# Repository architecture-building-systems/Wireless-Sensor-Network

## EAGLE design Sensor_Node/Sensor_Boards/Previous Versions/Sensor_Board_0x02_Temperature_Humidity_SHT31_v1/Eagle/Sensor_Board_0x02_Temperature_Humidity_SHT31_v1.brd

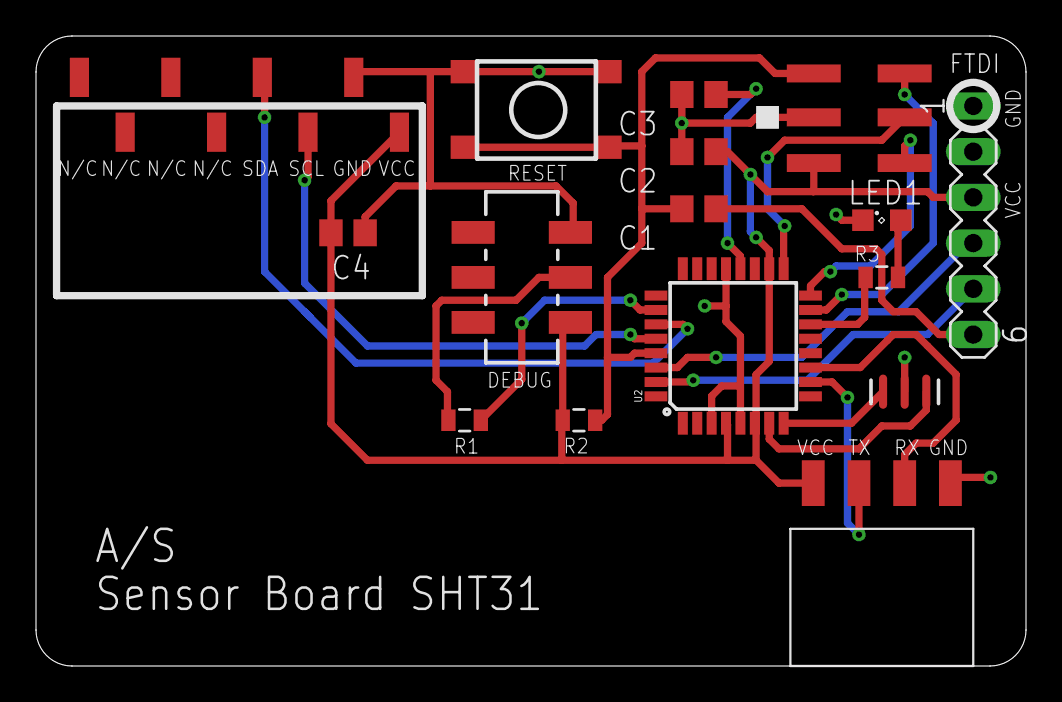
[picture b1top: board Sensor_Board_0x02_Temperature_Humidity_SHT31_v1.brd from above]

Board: 2 copper layers, 55.0 x 35.0 mm, 16 parts (0 on the bottom side), 20 nets.

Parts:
C1, C2, C3, C4: 100n; C0805
J1: M04_SMD_90
J4: ARDUINO_ISP; M-2X3
LED1: Red; SML0805
R1, R2: 10k; 0805
R3: 330; 0805
S1: Reset; M-PUSHBUTTON-SMD
S3: JS202011SCQN
SV1: MA06-1
U2: ATMEGA328P_TQFP; TQFP32-08
U$9: M08_SMD_STRAIGHT
Y1: 8MHZ; RESONATOR-SMD

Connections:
DBG_ENABLE: R1.2, U2.26
FTDI_RESET: C1.1, SV1.6
FTDI_RXI: SV1.4, U2.30
FTDI_TXO: SV1.5, U2.31
GND: C2.2, C3.2, C4.2, J1.4, J4.P$5, LED1.C, S1.1, S1.2, S3.3, SV1.1, SV1.2, U2.3, U2.5, U2.21, U$9.P7, Y1.2
L1: R3.2, U2.14
MCU_RXI: J1.3, U2.11
MCU_TXO: J1.2, U2.10
MISO: J4.P$1, U2.16
MOSI: J4.P$3, U2.15
unnamed: U2.8, Y1.3
unnamed: U2.7, Y1.1
unnamed: R1.1, S3.2
unnamed: C3.1, U2.20
unnamed: LED1.A, R3.1
RESET: C1.2, J4.P$4, R2.1, S1.3, S1.4, U2.29
SCK: J4.P$2, U2.17
SCL: U2.28, U$9.P6
SDA: U2.27, U$9.P5
VCC: C2.1, C4.1, J1.1, J4.P$6, R2.2, S3.1, SV1.3, U2.4, U2.6, U2.18, U$9.P8

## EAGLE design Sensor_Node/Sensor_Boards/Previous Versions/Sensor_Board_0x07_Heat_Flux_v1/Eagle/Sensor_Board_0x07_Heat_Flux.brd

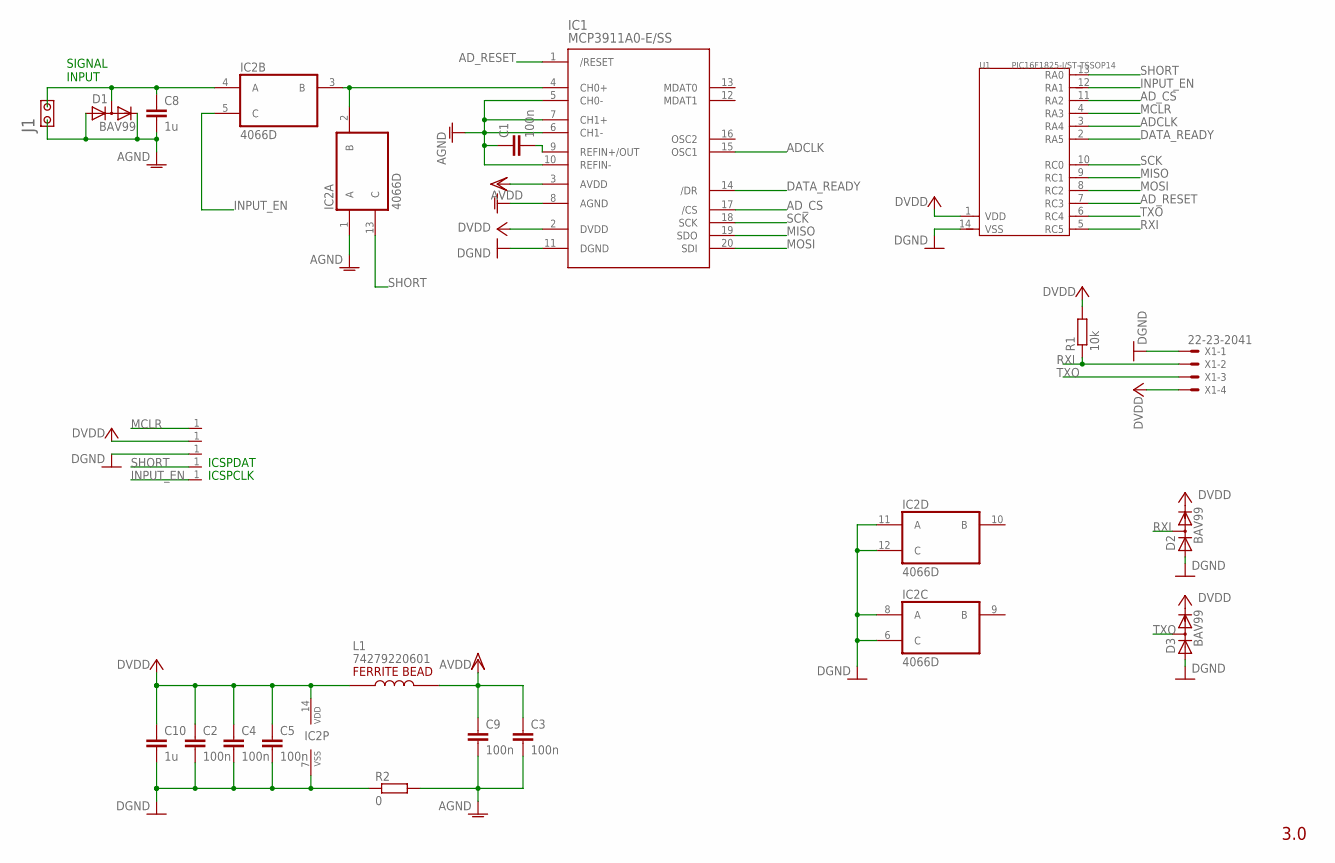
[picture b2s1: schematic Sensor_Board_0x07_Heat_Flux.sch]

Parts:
C1, C2, C3, C4, C5, C9: 100n; C0805
C8, C10: 1u; C0805
D1, D2, D3: BAV99; SOT23
IC1: MCP3911A0-E/SS; SSOP20
IC2: 4066D; SO14
J1: CON2X1
L1: 74279220601; 0805
PIN1, PIN2, PIN3, PIN4, PIN5: CON1X1
R1: 10k; M0805
R2: 0; M0805
U1: PIC16F1825-I/ST-TSSOP14; TSSOP14-0.65-5X4.4MM
X1: 22-23-2041

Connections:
ADCLK: IC1.15 (OSC1), U1.3 (RA4)
AD_CS: IC1.17 (/CS), U1.11 (RA2)
AD_RESET: IC1.1 (/RESET), U1.7 (RC3)
AGND: C1.1, C3.2, C8.2, C9.2, D1.1 (A), D1.2 (C), IC1.5 (CH0-), IC1.6 (CH1-), IC1.7 (CH1+), IC1.8 (AGND), IC1.10 (REFIN-), IC2.1 (A), J1.1, R2.2
AVDD: C3.1, C9.1, IC1.3 (AVDD), L1.2
DATA_READY: IC1.14 (/DR), U1.2 (RA5)
DGND: C2.2, C4.2, C5.2, C10.2, D2.1 (A), D3.1 (A), IC1.11 (DGND), IC2.6 (C), IC2.7 (VSS), IC2.8 (A), IC2.11 (A), IC2.12 (C), PIN3.1, R2.1, U1.14 (VSS), X1.1
DVDD: C2.1, C4.1, C5.1, C10.1, D2.2 (C), D3.2 (C), IC1.2 (DVDD), IC2.14 (VDD), L1.1, PIN2.1, R1.2, U1.1 (VDD), X1.4
INPUT_EN: IC2.5 (C), PIN5.1, U1.12 (RA1)
MCLR: PIN1.1, U1.4 (RA3)
MISO: IC1.19 (SDO), U1.9 (RC1)
MOSI: IC1.20 (SDI), U1.8 (RC2)
unnamed: C1.2, IC1.9 (REFIN+/OUT)
unnamed: IC1.4 (CH0+), IC2.2 (B), IC2.3 (B)
unnamed: C8.1, D1.3 (AC), IC2.4 (A), J1.2
RXI: D2.3 (AC), R1.1, U1.5 (RC5), X1.2
SCK: IC1.18 (SCK), U1.10 (RC0)
SHORT: IC2.13 (C), PIN4.1, U1.13 (RA0)
TXO: D3.3 (AC), U1.6 (RC4), X1.3

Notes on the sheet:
SIGNAL INPUT
ICSPCLK
ICSPDAT
3.0

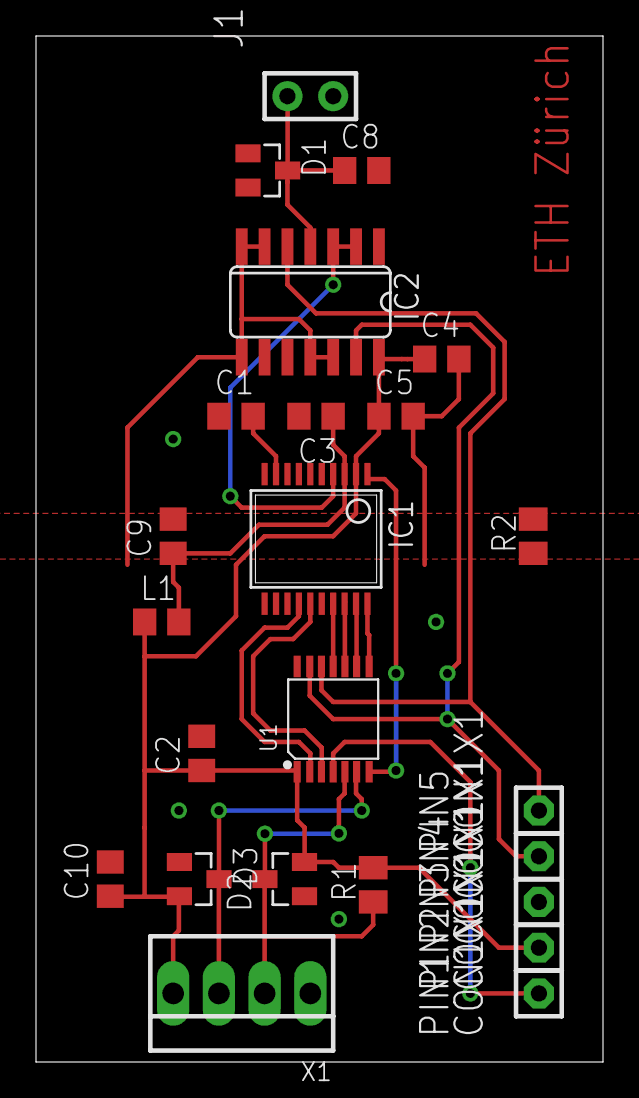
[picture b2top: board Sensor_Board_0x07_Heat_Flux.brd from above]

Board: 2 copper layers, 31.5 x 57.0 mm, 24 parts (0 on the bottom side), 19 nets.

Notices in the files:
parts and their libraries:
SparkFun-Passives: Licensing: Creative Commons ShareAlike 4.0 International - https://creativecommons.org/licenses/by-sa/4.0
